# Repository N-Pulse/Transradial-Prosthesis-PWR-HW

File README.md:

# Transradial Prosthesis Power Supply Board

This work is licensed under a <a rel="license" href="https://creativecommons.org/licenses/by/4.0/">Creative Commons Attribution 4.0 International License</a>.

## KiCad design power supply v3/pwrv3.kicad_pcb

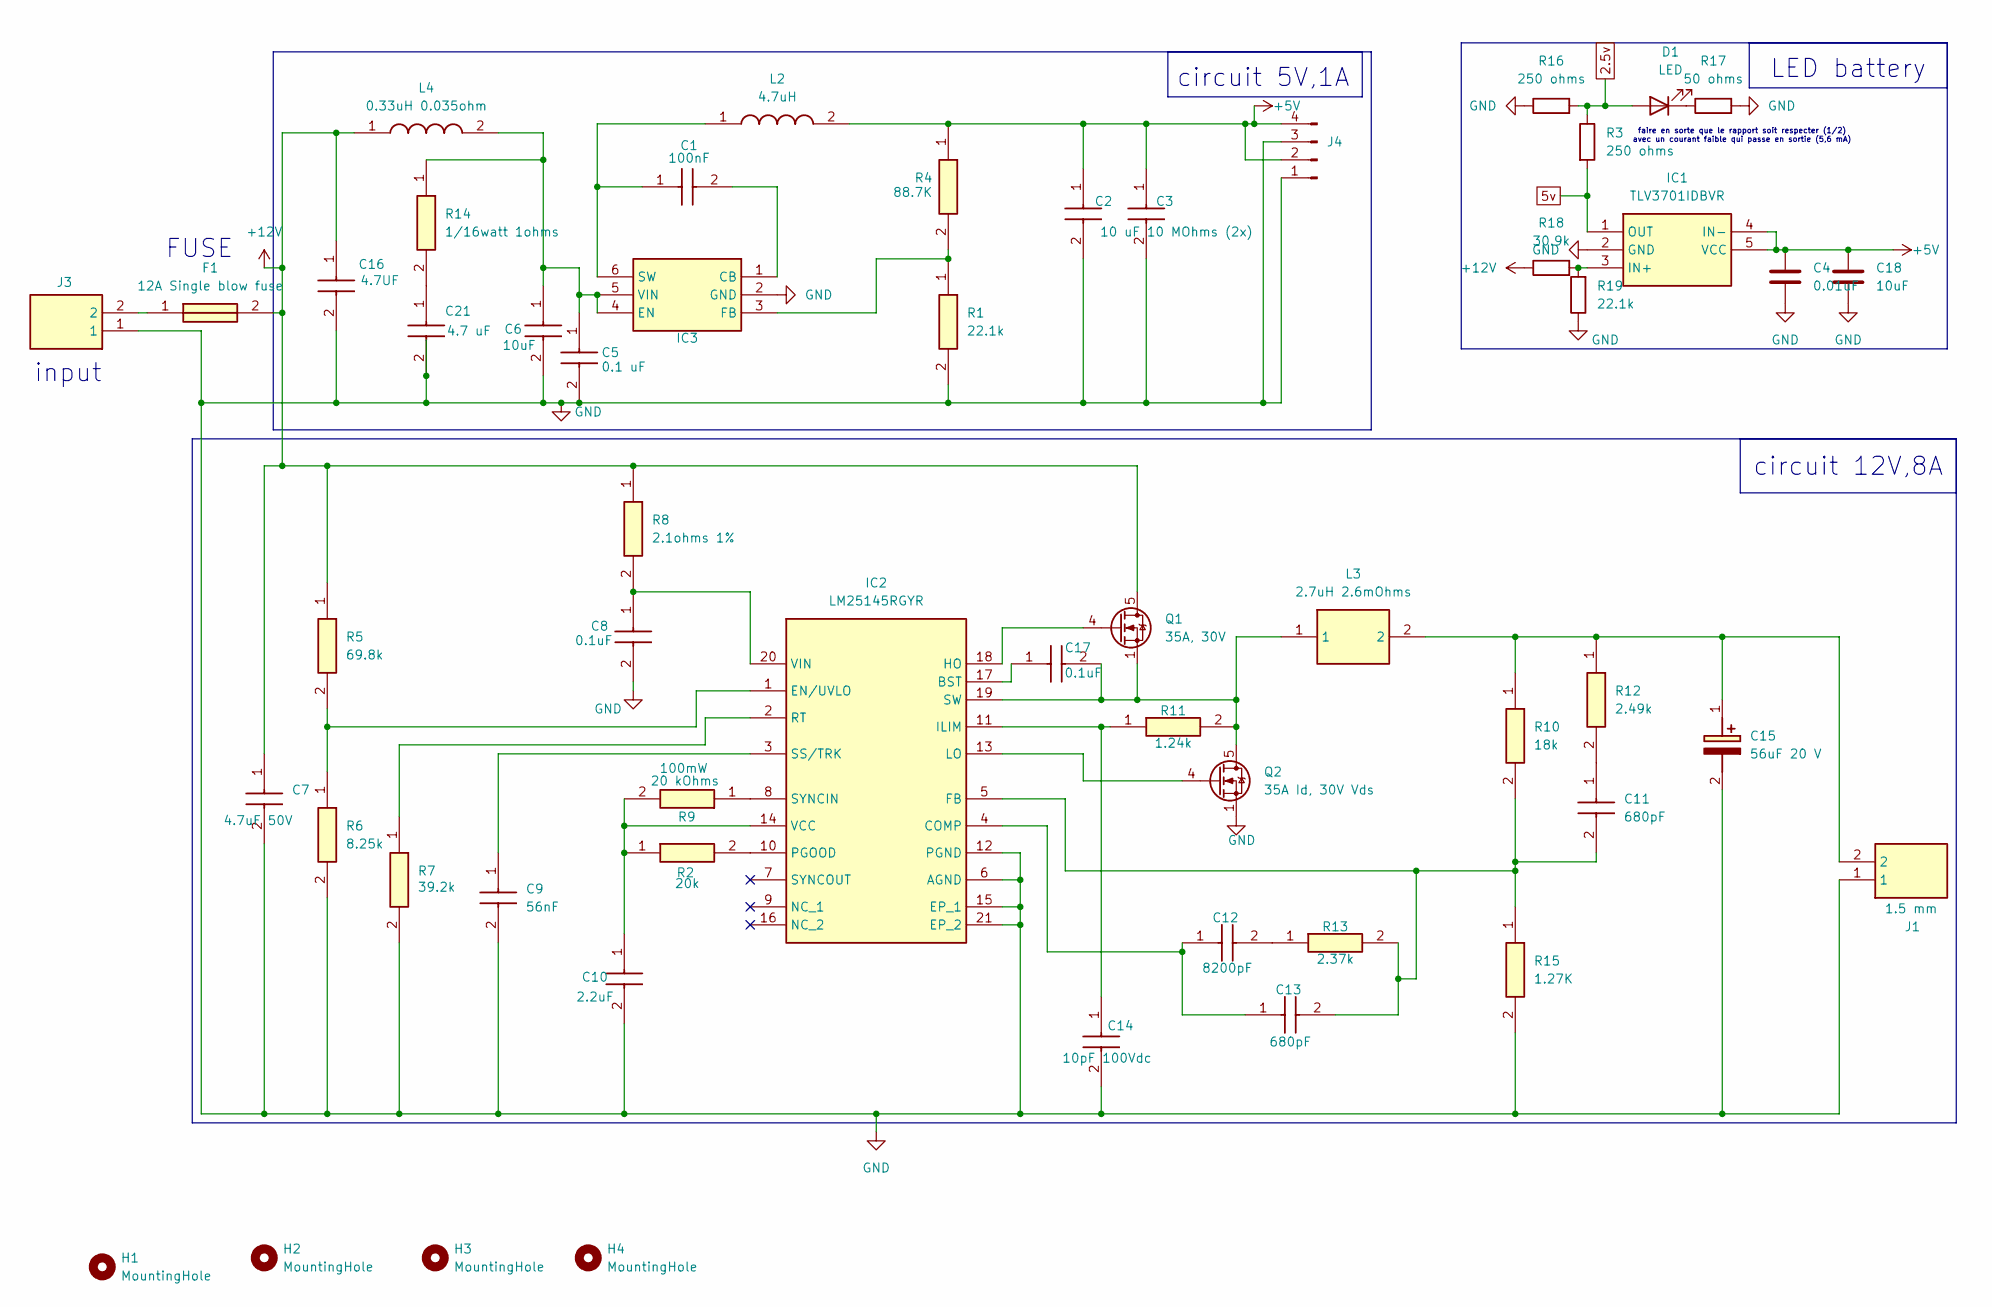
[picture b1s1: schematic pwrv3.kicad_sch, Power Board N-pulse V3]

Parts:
C1: 100nF; C_0402_1005Metric; Mouser Part Number N/A
C2: 10 uF 10 MOhms (2x); C_0805_2012Metric; Mouser Part Number 80-C0805C106K8P
C3: C0805C106K8PACTU (2X); C_0805_2012Metric; Mouser Part Number 80-C0805C106K8P
C4: 0.01uF; C_1206_3216Metric
C5: 0.1 uF; C_0603_1608Metric; Mouser Part Number 81-GRM188R72A104KA5J
C6: 10uF; C_0603_1608Metric; Mouser Part Number 810-C1608X5R1E106M
C7: 4.7uF 50V; C_1210_3225Metric; Mouser Part Number 81-GRM32R71H475KA88L
C8: CGA3E2X7R1H104K080AA; C_0603_1608Metric; Mouser Part Number 810-CGA3E2X7R1H104K
C9: 56nF; C_0402_1005Metric; Mouser Part Number 81-GRM155R71C563KA8D
C10: 2.2uF; C_0402_1005Metric; Mouser Part Number 810-C1005X5R1V225K
C11, C13: 680pF; C_0402_1005Metric; Mouser Part Number 810-CGA2B2X7R1H681K
C12: 8200pF; C_0402_1005Metric; Mouser Part Number 81-GRM155R71C822KA1D
C14: 10pF 100Vdc; C_0603_1608Metric; Manufacturer_Part_Number GRM1885C2A100JA01D
C15: 56uF 20 V; 16SVF82M; Mouser Part Number 667-20SVPF56MX
C16: 4.7UF; C_1206_3216Metric; Mouser Part Number 81-GRM31CR71H475KA2L
C17: 0.1uF; C_0402_1005Metric; Mouser Part Number 81-GCM1555C1H100FA6D
C18: 10uF; C_0805_2012Metric
C21: 4.7 uF; C_1210_3225Metric; Mouser Part Number 810-C3225X7S2A475M
D1: LED; D_1206_3216Metric
F1: SF-1206HH12M-2; Fuse_1206_3216Metric; Mouser Part Number 652-SF-1206HH12M-2
H1, H2, H3, H4: MountingHole; MountingHole_2.2mm_M2
IC1: TLV3701IDBVR; SOT95P280X145-5N; Mouser Part Number 595-TLV3701IDBVR
IC2: LM25145RGYR; RGY0020B; Mouser Part Number 595-LM25145RGYR
IC3: LMR50410YQDBVRQ1; SOT95P280X145-6N; Mouser Part Number 595-LMR50410YQDBVRQ1
J1: 1.5 mm; 1933189; Mouser Part Number 651-1933189
J3: 1933189; Mouser Part Number 651-1933189
J4: Conn_01x04_Pin 1.27mm; PinHeader_1x04_P2.54mm_Vertical
L2: 4.7uH; INDC3030X200N; Mouser Part Number 710-74438336047
L3: 2.7uH 2.6mOhms; SER1360272KLD; Mouser Part Number 994-SER1360-272KLD
L4: 0.33uH 0.035ohm; L_1210_3225Metric; Mouser Part Number 810-NLCV32TR33MEFRD
Q1: 35A, 30V; VSON-8_3.3x3.3mm_P0.65mm_NexFET
Q2: 35A Id, 30V Vds; VSON-8_3.3x3.3mm_P0.65mm_NexFET
R1: 22.1k; R_0402_1005Metric; Mouser Part Number 71-CRCW0402-22.1K-E3
R2: 20k; R_0603_1608Metric; Mouser Part Number 603-RC0603FR-0720KL
R3, R16: 250 ohms; R_0603_1608Metric
R4: 88.7K; R_0402_1005Metric; Mouser Part Number 71-CRCW0402-88.7K-E3
R5: 69.8k; R_0402_1005Metric; Mouser Part Number 71-CRCW0402-69.8K-E3
R6: 8.25k; R_0603_1608Metric; Mouser Part Number 71-CRCW0603-8.25K-E3
R7: 39.2k; R_0402_1005Metric; Mouser Part Number 71-CRCW0402-39.2K-E3
R8: 2.1ohms 1%; R_0603_1608Metric; Mouser Part Number 71-CRCW06032R10FKEA
R9: 20 kOhms; R_0603_1608Metric; Mouser Part Number 603-RC0603FR-0720KL
R10: 18k; R_0603_1608Metric; Mouser Part Number 603-RC0603FR-0718KL
R11: 1.24k; R_0402_1005Metric; Mouser Part Number 71-CRCW0402-1.24K-E3
R12: 2.49k; R_0402_1005Metric; Mouser Part Number 71-CRCW0402-2.49K-E3
R13: 2.37k; R_0402_1005Metric; Mouser Part Number 71-CRCW0402-2.37K-E3
R14: 1/16watt 1ohms; R_0402_1005Metric; Mouser Part Number 71-CRCW0402-1-E3
R15: 1.27K; R_0402_1005Metric; Mouser Part Number 71-CRCW0402-1.27K-E3
R17: 50 ohms; R_0402_1005Metric
R18: 30.9k; R_0402_1005Metric
R19: 22.1k; R_0402_1005Metric

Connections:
2.5v: D1.2 (A), R3.1, R16.2
5v: IC1.1 (OUT), R3.2
+5V: C2.1, C3.1, C4.1, C18.1, IC1.4 (IN-), IC1.5 (VCC), J4.2, J4.4, L2.2, R4.1
+12V: C7.1, C16.1, F1.2, L4.1, Q1.5 (D), R5.1, R8.1, R18.1
GND: C2.2, C3.2, C4.2, C5.2, C6.2, C7.2, C8.2, C9.2, C10.2, C14.2, C15.2 (-), C16.2, C18.2, C21.2, IC1.2 (GND), IC2.6 (AGND), IC2.12 (PGND), IC2.15 (EP_1), IC2.21 (EP_2), IC3.2 (GND), J1.1, J3.1, J4.1, J4.3, Q2.1 (S), Q2.2 (S), Q2.3 (S), R1.2, R6.2, R7.2, R15.2, R16.1, R17.2, R19.1
unnamed: C11.1, R12.2
unnamed: C12.2, R13.1
unnamed: C15.1 (+), J1.2, L3.2, R10.1, R12.1
unnamed: C21.1, R14.2
unnamed: D1.1 (K), R17.1
unnamed: F1.1, J3.2
unnamed: IC1.3 (IN+), R18.2, R19.2
unnamed: C17.1, IC2.17 (BST)
unnamed: C12.1, C13.1, IC2.4 (COMP)
unnamed: IC2.1 (EN/UVLO), R5.2, R6.1
unnamed: C11.2, C13.2, IC2.5 (FB), R10.2, R13.2, R15.1
unnamed: IC2.18 (HO), Q1.4 (G)
unnamed: C14.1, IC2.11 (ILIM), R11.1
unnamed: IC2.13 (LO), Q2.4 (G)
unnamed: IC2.10 (PGOOD), R2.2
unnamed: IC2.2 (RT), R7.1
unnamed: C9.1, IC2.3 (SS/TRK)
unnamed: C17.2, IC2.19 (SW), L3.1, Q1.1 (S), Q1.2 (S), Q1.3 (S), Q2.5 (D), R11.2
unnamed: IC2.8 (SYNCIN), R9.1
unnamed: C10.1, IC2.14 (VCC), R2.1, R9.2
unnamed: C8.1, IC2.20 (VIN), R8.2
unnamed: C1.2, IC3.1 (CB)
unnamed: C5.1, C6.1, IC3.4 (EN), IC3.5 (VIN), L4.2, R14.1
unnamed: IC3.3 (FB), R1.1, R4.2
unnamed: C1.1, IC3.6 (SW), L2.1

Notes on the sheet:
input
circuit 12V,8A
circuit 5V,1A
LED battery
faire en sorte que le rapport soit respecter (1/2) avec un courant faible qui passe en sortie (5,6 mA)
FUSE

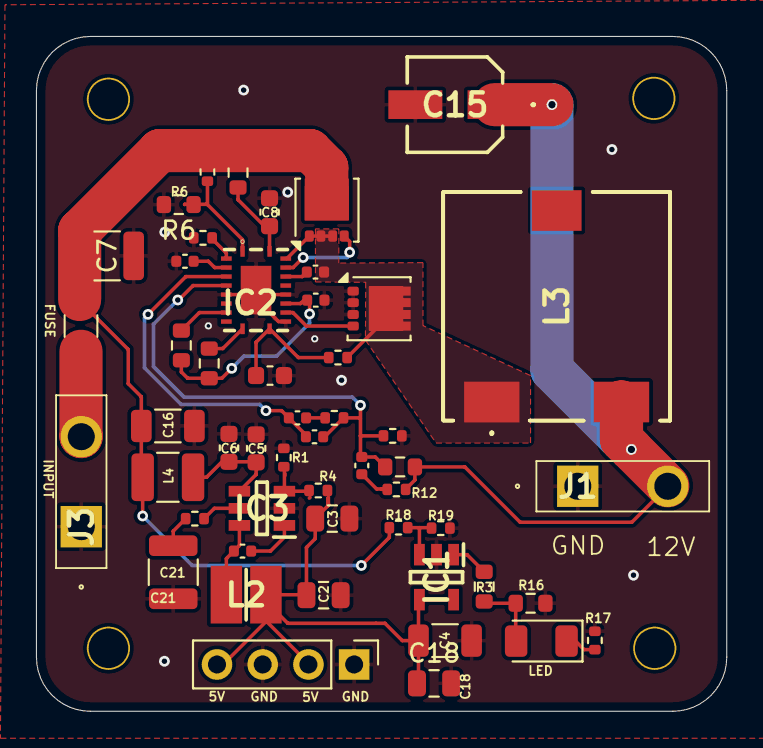
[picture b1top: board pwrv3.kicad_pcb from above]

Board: 2 copper layers, 38.3 x 37.5 mm, 55 parts (0 on the bottom side), 30 nets.

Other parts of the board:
H2#2, H3#2: MountingHole; MountingHole_2.2mm_M2

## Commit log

2025-02-21 the power board
    maybe the component will not be right
2025-02-25 update report pdf
2025-02-26 version smaller of the PCB
2025-03-03 v2 de la board
2025-03-03 v2 of board
2025-03-07 last version of pcb and gerber files
2025-03-07 add measurement annotations and move the top right screw up by 0.27mm for standardisation
2025-03-08 add 2 2.4mm screw holes and regenerate gerber files
2025-03-12 add license
2025-04-01 new schematics version
2025-04-01 add the LED to electronics schematics
2025-04-03 new layout and pin moved
2025-04-04 entree comparateur 5V
2025-04-06 retracing
2025-04-06 flip Q2 transistor
2025-04-08 board joe v2 finish
2025-04-08 size vias updated
2025-04-17 tous les noms
2025-04-24 epaisseur de cuivre
2025-04-24 gerbers files
2025-04-24 slightly move components on battery trace and add ground vias around GND pins
2025-05-28 capa bst updated
